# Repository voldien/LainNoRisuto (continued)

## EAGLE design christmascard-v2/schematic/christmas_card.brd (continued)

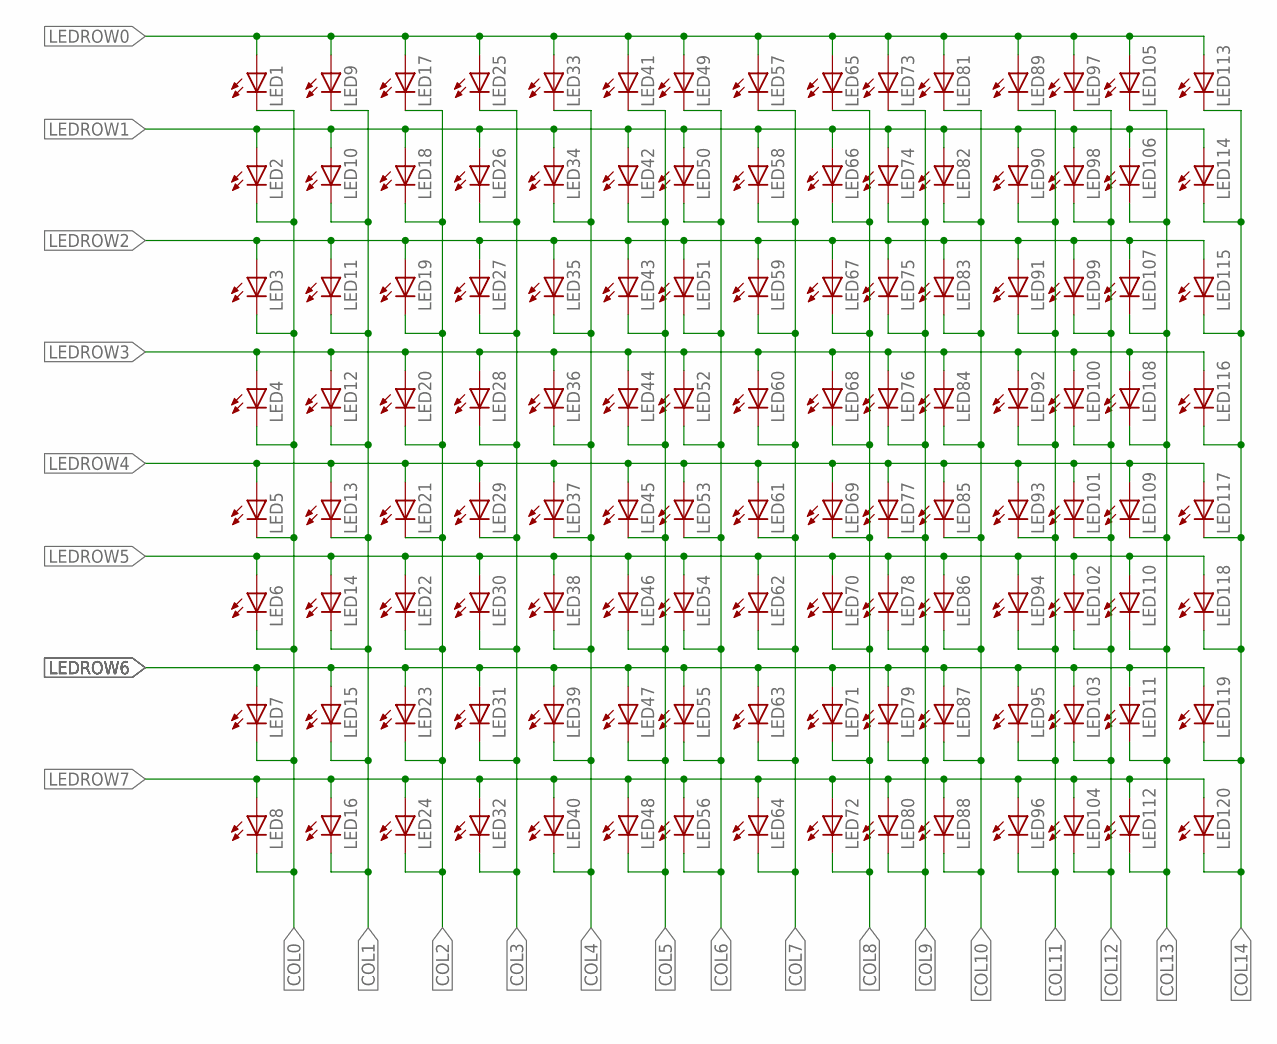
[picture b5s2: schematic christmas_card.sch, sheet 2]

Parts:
LED1, LED2, LED3, LED4, LED5, LED6, LED7, LED8, LED9, LED10, LED11, LED12, LED13, LED14, LED15, LED16, LED17, LED18, LED19, LED20, LED21, LED22, LED23, LED24, LED25, LED26, LED27, LED28, LED29, LED30, LED31, LED32, LED33, LED34, LED35, LED36, LED37, LED38, LED39, LED40, LED41, LED42, LED43, LED44, LED45, LED46, LED47, LED48, LED49, LED50, LED51, LED52, LED53, LED54, LED55, LED56, LED57, LED58, LED59, LED60, LED61, LED62, LED63, LED64, LED65, LED66, LED67, LED68, LED69, LED70, LED71, LED72, LED73, LED74, LED75, LED76, LED77, LED78, LED79, LED80, LED81, LED82, LED83, LED84, LED85, LED86, LED87, LED88, LED89, LED90, LED91, LED92, LED93, LED94, LED95, LED96, LED97, LED98, LED99, LED100, LED101, LED102, LED103, LED104, LED105, LED106, LED107, LED108, LED109, LED110, LED111, LED112, LED113, LED114, LED115, LED116, LED117, LED118, LED119, LED120: LED1206; LED-1206

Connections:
COL0: LED1.C, LED2.C, LED3.C, LED4.C, LED5.C, LED6.C, LED7.C, LED8.C; also elsewhere on the board
COL1: LED9.C, LED10.C, LED11.C, LED12.C, LED13.C, LED14.C, LED15.C, LED16.C; also elsewhere on the board
COL2: LED17.C, LED18.C, LED19.C, LED20.C, LED21.C, LED22.C, LED23.C, LED24.C; also elsewhere on the board
COL3: LED25.C, LED26.C, LED27.C, LED28.C, LED29.C, LED30.C, LED31.C, LED32.C; also elsewhere on the board
COL4: LED33.C, LED34.C, LED35.C, LED36.C, LED37.C, LED38.C, LED39.C, LED40.C; also elsewhere on the board
COL5: LED41.C, LED42.C, LED43.C, LED44.C, LED45.C, LED46.C, LED47.C, LED48.C; also elsewhere on the board
COL6: LED49.C, LED50.C, LED51.C, LED52.C, LED53.C, LED54.C, LED55.C, LED56.C; also elsewhere on the board
COL7: LED57.C, LED58.C, LED59.C, LED60.C, LED61.C, LED62.C, LED63.C, LED64.C; also elsewhere on the board
COL8: LED65.C, LED66.C, LED67.C, LED68.C, LED69.C, LED70.C, LED71.C, LED72.C; also elsewhere on the board
COL9: LED73.C, LED74.C, LED75.C, LED76.C, LED77.C, LED78.C, LED79.C, LED80.C; also elsewhere on the board
COL10: LED81.C, LED82.C, LED83.C, LED84.C, LED85.C, LED86.C, LED87.C, LED88.C; also elsewhere on the board
COL11: LED89.C, LED90.C, LED91.C, LED92.C, LED93.C, LED94.C, LED95.C, LED96.C; also elsewhere on the board
COL12: LED97.C, LED98.C, LED99.C, LED100.C, LED101.C, LED102.C, LED103.C, LED104.C; also elsewhere on the board
COL13: LED105.C, LED106.C, LED107.C, LED108.C, LED109.C, LED110.C, LED111.C, LED112.C; also elsewhere on the board
COL14: LED113.C, LED114.C, LED115.C, LED116.C, LED117.C, LED118.C, LED119.C, LED120.C; also elsewhere on the board
LEDROW0: LED1.A, LED9.A, LED17.A, LED25.A, LED33.A, LED41.A, LED49.A, LED57.A, LED65.A, LED73.A, LED81.A, LED89.A, LED97.A, LED105.A, LED113.A; also elsewhere on the board
LEDROW1: LED2.A, LED10.A, LED18.A, LED26.A, LED34.A, LED42.A, LED50.A, LED58.A, LED66.A, LED74.A, LED82.A, LED90.A, LED98.A, LED106.A, LED114.A; also elsewhere on the board
LEDROW2: LED3.A, LED11.A, LED19.A, LED27.A, LED35.A, LED43.A, LED51.A, LED59.A, LED67.A, LED75.A, LED83.A, LED91.A, LED99.A, LED107.A, LED115.A; also elsewhere on the board
LEDROW3: LED4.A, LED12.A, LED20.A, LED28.A, LED36.A, LED44.A, LED52.A, LED60.A, LED68.A, LED76.A, LED84.A, LED92.A, LED100.A, LED108.A, LED116.A; also elsewhere on the board
LEDROW4: LED5.A, LED13.A, LED21.A, LED29.A, LED37.A, LED45.A, LED53.A, LED61.A, LED69.A, LED77.A, LED85.A, LED93.A, LED101.A, LED109.A, LED117.A; also elsewhere on the board
LEDROW5: LED6.A, LED14.A, LED22.A, LED30.A, LED38.A, LED46.A, LED54.A, LED62.A, LED70.A, LED78.A, LED86.A, LED94.A, LED102.A, LED110.A, LED118.A; also elsewhere on the board
LEDROW6: LED7.A, LED15.A, LED23.A, LED31.A, LED39.A, LED47.A, LED55.A, LED63.A, LED71.A, LED79.A, LED87.A, LED95.A, LED103.A, LED111.A, LED119.A; also elsewhere on the board
LEDROW7: LED8.A, LED16.A, LED24.A, LED32.A, LED40.A, LED48.A, LED56.A, LED64.A, LED72.A, LED80.A, LED88.A, LED96.A, LED104.A, LED112.A, LED120.A; also elsewhere on the board

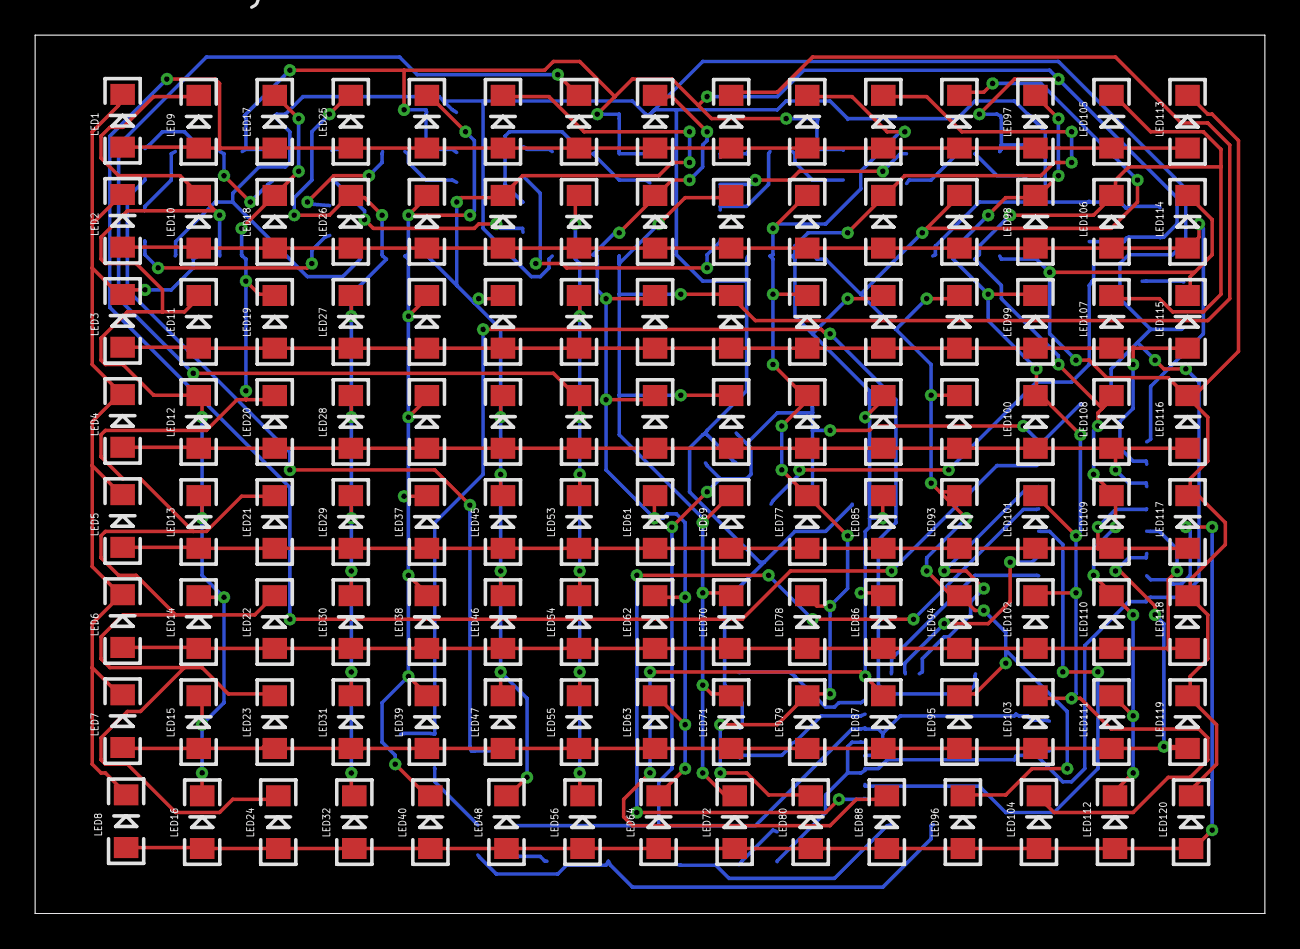
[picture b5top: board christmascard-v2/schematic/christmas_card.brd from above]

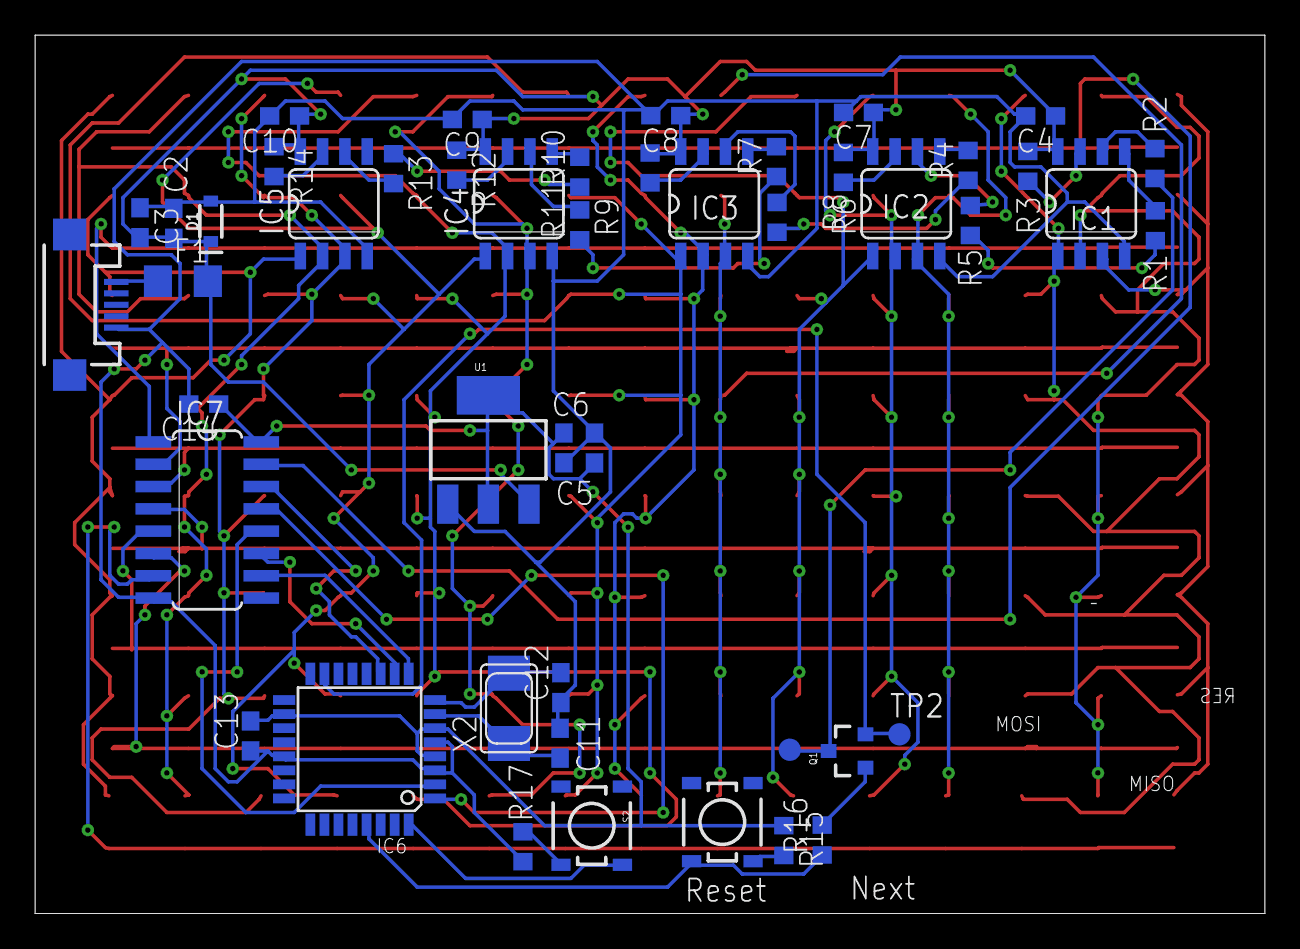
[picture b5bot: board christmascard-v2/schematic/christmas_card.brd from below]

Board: 2 copper layers, 70.0 x 50.0 mm, 167 parts (47 on the bottom side), 59 nets.

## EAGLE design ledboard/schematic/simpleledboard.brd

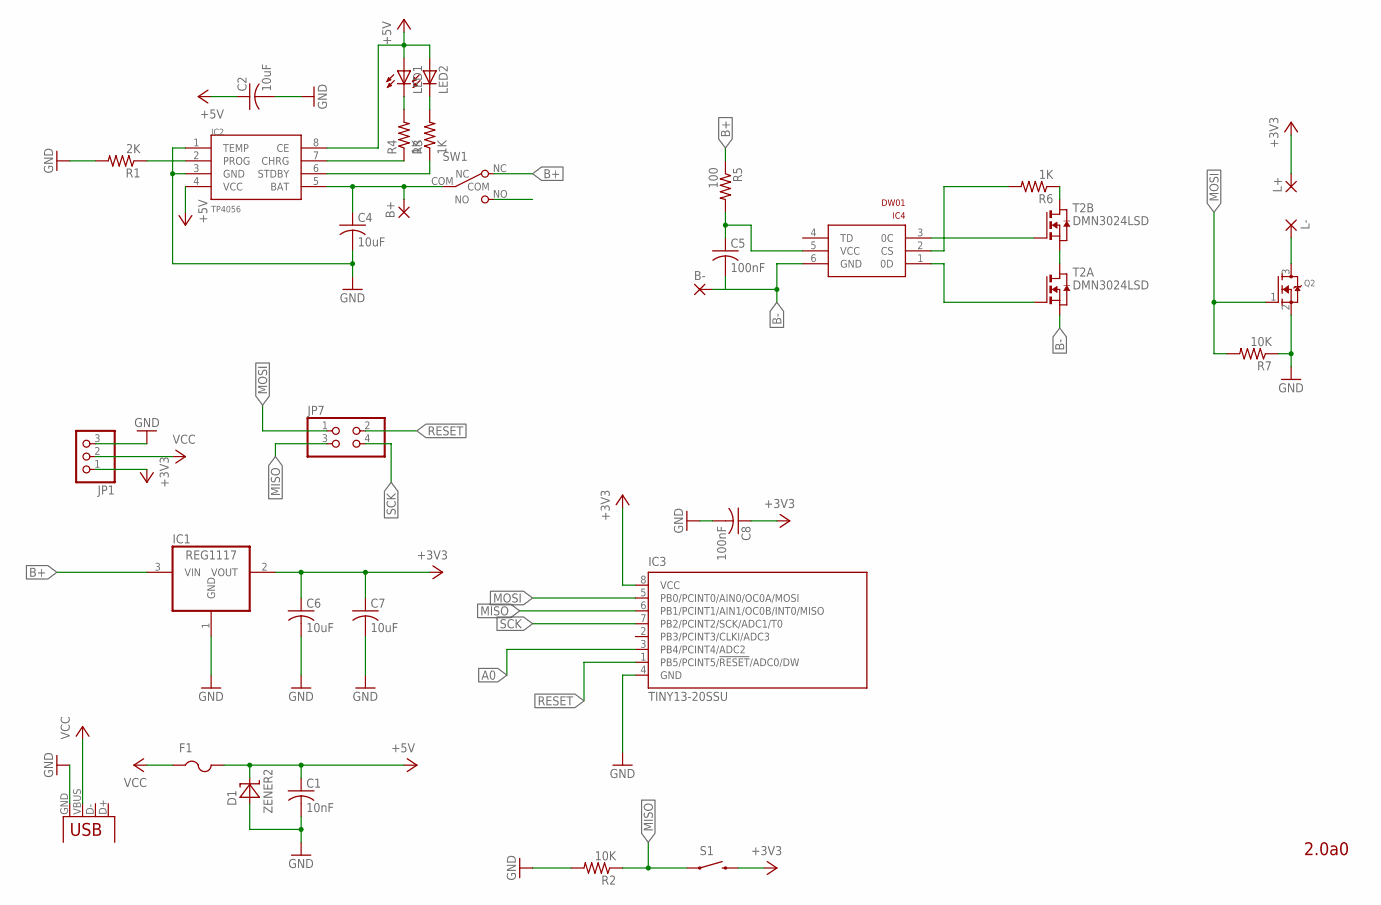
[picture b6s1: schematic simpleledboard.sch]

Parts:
B+: WIREPADSMD1,27-254; SMD1,27-2,54
B-: WIREPADSMD1,27-254; SMD1,27-2,54
C1: 10nF; C0603
C2, C4, C6, C7: 10uF; C0603
C5, C8: 100nF; C0603
D1: ZENER2; SOD123
F1: PTCFUSE-1206; R1206
IC1: REG1117; SOT223
IC2: TP4056; SOP-8
IC3: TINY13-20SSU; 8S1
IC4: DW01; SOT23-6
JP1: PINHD-1X3CB; 1X03-CLEANBIG
JP7: PINHD-2X2; 2X02
L+: SMD2; SMD1,27-2,54
L-: SMD2; SMD1,27-2,54
LED1, LED2: LED0603; LED-0603
Q2: MOSFET-NREFLOW; SOT23
R1: 2K; R0603
R2, R7: 10K; R0603
R3, R4, R6: 1K; R0603
R5: 100; R1206
S1: SWITCH-MOMENTARY-2SMD-4.6X2.8MM; TACTILE_SWITCH_SMD_4.6X2.8MM
SW1: SW_SLIDE; SLIDE_SWITCH_SMD
T2: DMN3024LSD; TSSOP-8
X2: USB-MICROB

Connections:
+3V3: C6.1, C7.1, C8.1, IC1.2 (VOUT), IC3.8 (VCC), JP1.1, L+.1, S1.3 (2), S1.4 (2)
+5V: C1.1, C2.1, D1.C, F1.2, IC2.4 (VCC), IC2.8 (CE), LED1.A, LED2.A
A0: IC3.3 (PB4/PCINT4/ADC2)
B+: IC1.3 (VIN), R5.1, SW1.NC
B+TMP: B+.1, C4.1, IC2.5 (BAT), SW1.COM
B-: B-.1, C5.2, IC4.6 (GND), T2.2 (S), T2.3 (S)
GND: C1.2, C2.2, C4.2, C6.2, C7.2, C8.2, D1.A, IC1.1 (GND), IC2.1 (TEMP), IC2.3 (GND), IC3.4 (GND), JP1.3, Q2.2 (S), R1.2, R2.2, R7.1, X2.GND
MISO: IC3.6 (PB1/PCINT1/AIN1/OC0B/INT0/MISO), JP7.3, R2.1, S1.1, S1.2 (1)
MOSI: IC3.5 (PB0/PCINT0/AIN0/OC0A/MOSI), JP7.1, Q2.1 (G), R7.2
unnamed: IC2.7 (CHRG), R4.1
unnamed: IC4.1 (0D), T2.4 (G)
unnamed: T2.1 (D), T2.6 (S), T2.7 (S)
unnamed: LED1.C, R4.2
unnamed: IC4.3 (0C), T2.5 (G)
unnamed: IC4.2 (CS), R6.2
unnamed: C5.1, IC4.5 (VCC), R5.2
unnamed: R6.1, T2.8 (D)
unnamed: L-.1, Q2.3 (D)
unnamed: LED2.C, R3.2
unnamed: IC2.6 (STDBY), R3.1
unnamed: IC2.2 (PROG), R1.1
RESET: IC3.1 (PB5/PCINT5/!RESET!/ADC0/DW), JP7.2
SCK: IC3.7 (PB2/PCINT2/SCK/ADC1/T0), JP7.4
VCC: F1.1, JP1.2, X2.VBUS

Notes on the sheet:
2.0a0

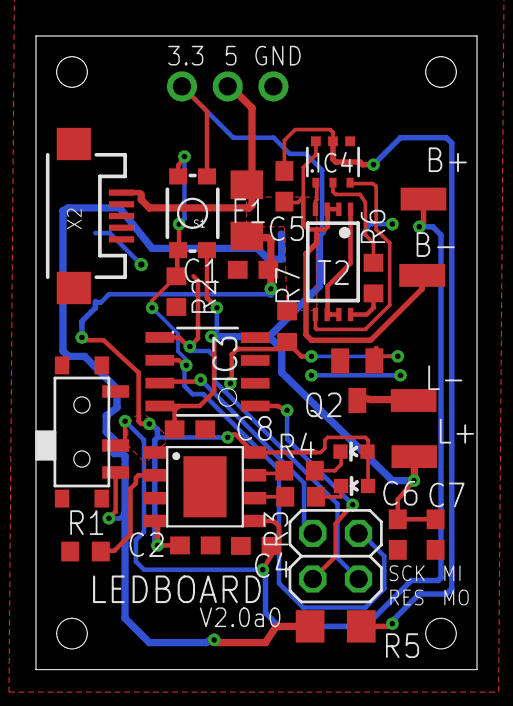
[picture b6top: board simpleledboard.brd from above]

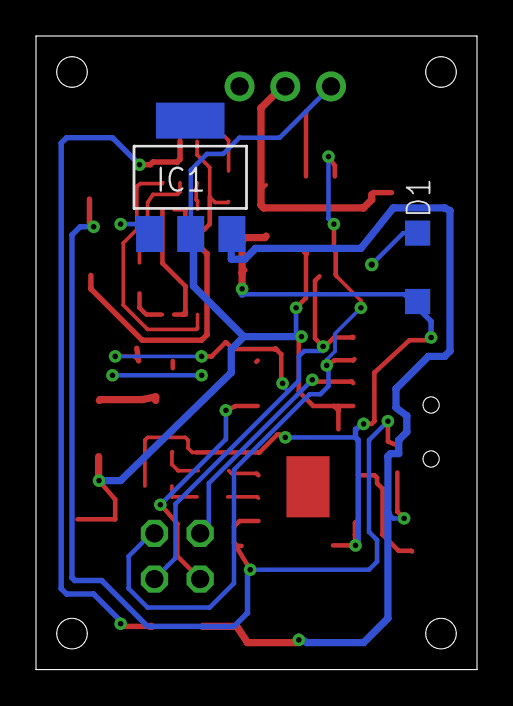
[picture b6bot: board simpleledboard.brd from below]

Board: 2 copper layers, 24.5 x 35.2 mm, 33 parts (2 on the bottom side), 23 nets.

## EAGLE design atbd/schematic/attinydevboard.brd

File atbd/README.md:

ledboard
---
ledboard is as the name implies. A board for driving LED's. It was influcended by IKEA's LED strip that useage Alkine battery. Even though LED's are power effiecent it's still a waste of material of needing to replace these batteries.
That's why this ledboard has support to use either lithium ion battery for portability or via USB. 

Features

---
SPI pins.
LED pads.
Battery Pads.
Attiny13

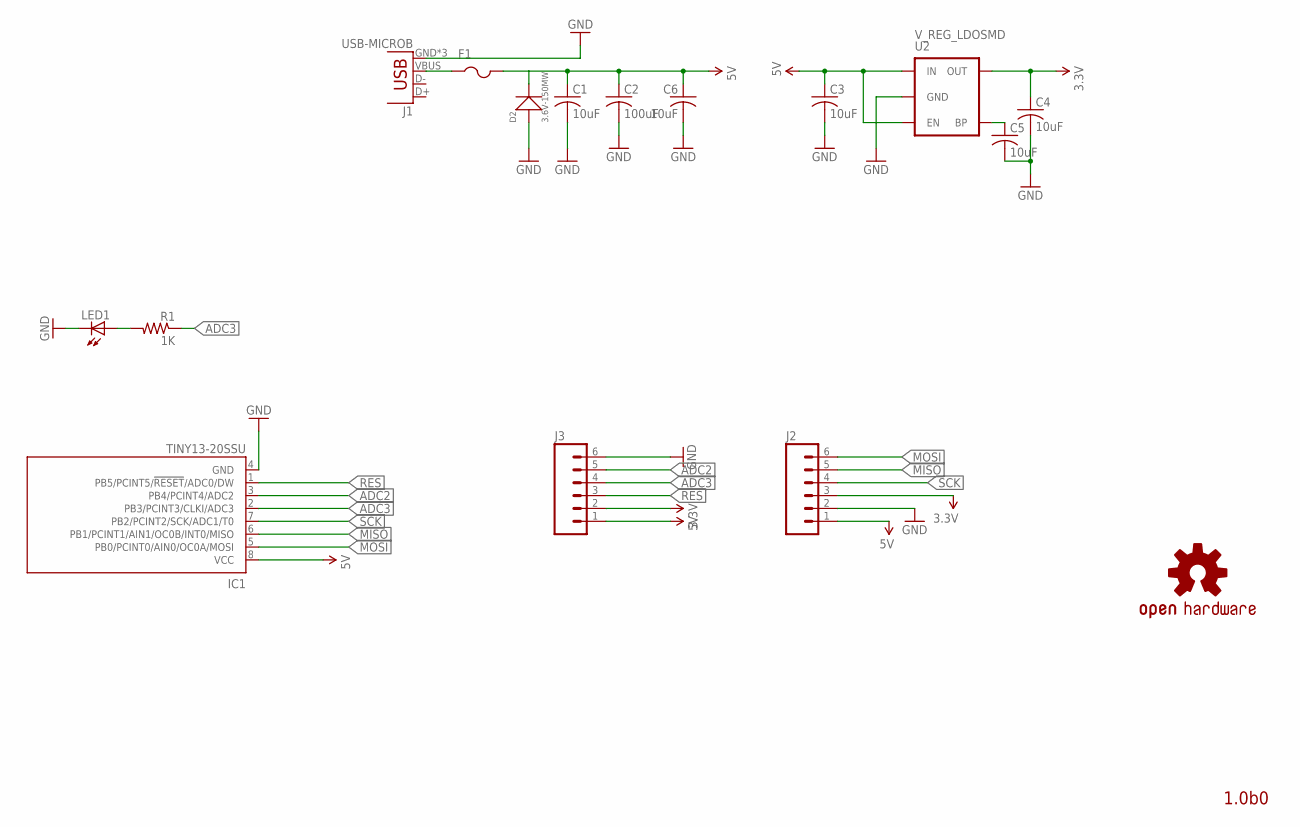
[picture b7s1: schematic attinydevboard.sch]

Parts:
C1, C3, C4, C5, C6: 10uF; C0603
C2: 100uF; C0603
D2: 3.6V-150MW; SOD-523
F1: PTCFUSE-1206; R1206
IC1: TINY13-20SSU; 8S1
J1: USB-MICROB
J2, J3: M06SIP; 1X06
LED1: LED0603; LED-0603
R1: 1K; R0603
U2: V_REG_LDOSMD; SOT23-5
U$2: OSHW-LOGOS; OSHW-LOGO-S

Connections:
3.3V: C4.1, J2.3, J3.2, U2.5 (OUT)
5V: C1.1, C2.1, C3.1, C6.1, D2.-, F1.2, IC1.8 (VCC), J2.1, J3.1, U2.1 (IN), U2.3 (EN)
ADC2: IC1.3 (PB4/PCINT4/ADC2), J3.5
ADC3: IC1.2 (PB3/PCINT3/CLKI/ADC3), J3.4, R1.1
GND: C1.2, C2.2, C3.2, C4.2, C5.2, C6.2, D2.+, IC1.4 (GND), J1.GND, J1.MT1 (GND), J1.MT2 (GND), J2.2, J3.6, LED1.C, U2.2 (GND)
MISO: IC1.6 (PB1/PCINT1/AIN1/OC0B/INT0/MISO), J2.5
MOSI: IC1.5 (PB0/PCINT0/AIN0/OC0A/MOSI), J2.6
unnamed: LED1.A, R1.2
unnamed: F1.1, J1.VBUS
unnamed: C5.1, U2.4 (BP)
RES: IC1.1 (PB5/PCINT5/!RESET!/ADC0/DW), J3.3
SCK: IC1.7 (PB2/PCINT2/SCK/ADC1/T0), J2.4

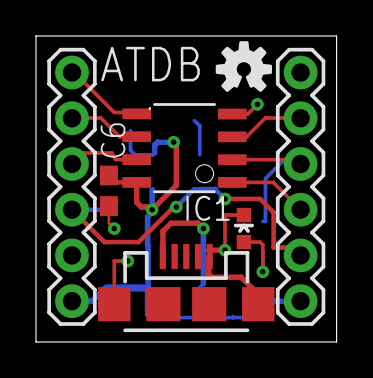
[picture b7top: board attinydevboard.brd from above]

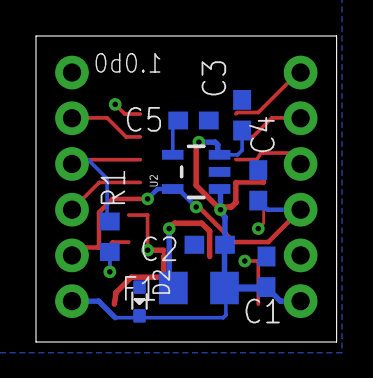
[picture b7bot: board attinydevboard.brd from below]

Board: 2 copper layers, 16.7 x 17.0 mm, 16 parts (9 on the bottom side), 12 nets.
